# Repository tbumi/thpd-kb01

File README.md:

# thpd-kb01

My very first mechanical keyboard designed from scratch!

## PCB

The PCB design files are made with KiCad v5.1.12.

### Features

- STM32 Microcontroller (STM32F072C8T6)
- Rotary encoder
- USB-C connector
- NHD-C12832A1Z (128x32 LCD) display (not confirmed working)

## Case

The case files are made with Inkscape. They are available in the `case/` subdirectory.

## License

Licensed under the CERN Open Hardware Licence Version 2 - Strongly Reciprocal. A copy of
the license is included in this repository.

## Firmware

This keyboard uses the QMK firmware. See the firmware in the fork here:
https://github.com/tbumi/qmk_firmware/tree/thpd-kb01/keyboards/thpd_kb01

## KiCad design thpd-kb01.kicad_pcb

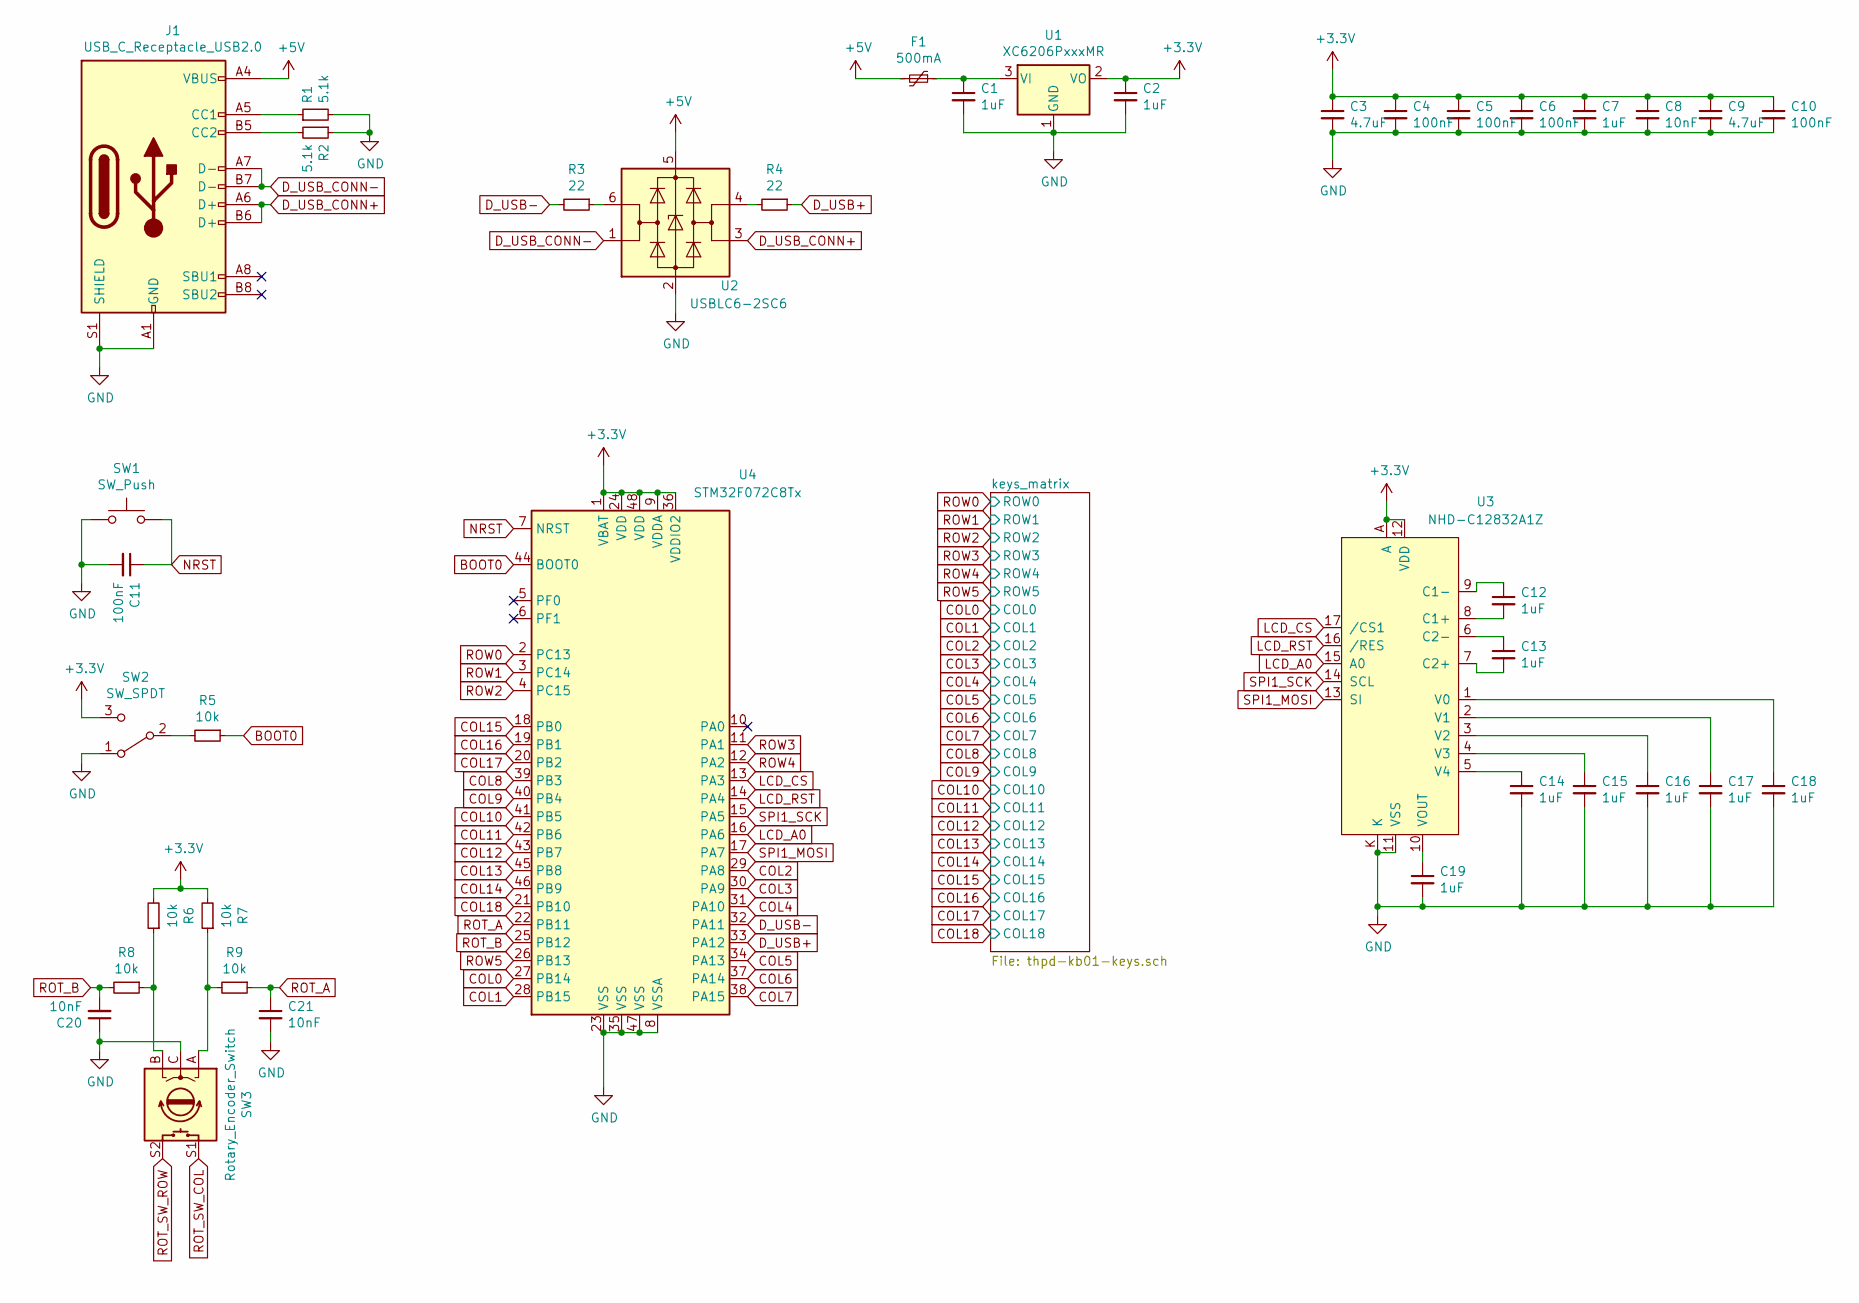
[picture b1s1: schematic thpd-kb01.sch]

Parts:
C1, C2, C7, C12, C13, C14, C15, C16, C17, C18, C19: 1uF; C_0402_1005Metric; LCSC Part # C52923
C3, C9: 4.7uF; C_0402_1005Metric; LCSC Part # C23733
C4, C5, C6, C10, C11: 100nF; C_0402_1005Metric; LCSC Part # C1525
C8, C20, C21: 10nF; C_0402_1005Metric; LCSC Part # C15195
F1: 500mA; Fuse_0603_1608Metric; LCSC Part # C135321
J1: USB_C_Receptacle_USB2.0; USB_C_Receptacle_HRO_TYPE-C-31-M-12; LCSC Part # C165948
R1, R2: 5.1k; R_0402_1005Metric; LCSC Part # C25905
R3, R4: 22; R_0402_1005Metric; LCSC Part # C25092
R5, R6, R7, R8, R9: 10k; R_0603_1608Metric; LCSC Part # C25804
SW1: SW_Push; SW_Push_SPST_NO_Alps_SKRK; LCSC Part # C202388
SW2: SW_SPDT; SW_SPDT_K3-1296S-E1; LCSC Part # C128955
SW3: Rotary_Encoder_Switch; RotaryEncoder_Alps_EC11E-Switch_Vertical_H20mm
U1: XC6206PxxxMR; SOT-23; LCSC Part # C5446
U2: USBLC6-2SC6; SOT-23-6; LCSC Part # C2827654
U3: NHD-C12832A1Z
U4: STM32F072C8Tx; LQFP-48_7x7mm_P0.5mm

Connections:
+3V3: C2.1, C3.1, C4.1, C5.1, C6.1, C7.1, C8.1, C9.1, C10.1, R6.2, R7.2, SW2.3 (C), U1.2 (VO), U3.12 (VDD), U3.A, U4.1 (VBAT), U4.9 (VDDA), U4.24 (VDD), U4.36 (VDDIO2), U4.48 (VDD)
+5V: F1.2, J1.A4 (VBUS), J1.A9 (VBUS), J1.B4 (VBUS), J1.B9 (VBUS), U2.5 (VBUS)
BOOT0: R5.1, U4.44 (BOOT0)
COL0: U4.27 (PB14); also elsewhere on the board
COL1: U4.28 (PB15); also elsewhere on the board
COL2: U4.29 (PA8); also elsewhere on the board
COL3: U4.30 (PA9); also elsewhere on the board
COL4: U4.31 (PA10); also elsewhere on the board
COL5: U4.34 (PA13); also elsewhere on the board
COL6: U4.37 (PA14); also elsewhere on the board
COL7: U4.38 (PA15); also elsewhere on the board
COL8: U4.39 (PB3); also elsewhere on the board
COL9: U4.40 (PB4); also elsewhere on the board
COL10: U4.41 (PB5); also elsewhere on the board
COL11: U4.42 (PB6); also elsewhere on the board
COL12: U4.43 (PB7); also elsewhere on the board
COL13: U4.45 (PB8); also elsewhere on the board
COL14: U4.46 (PB9); also elsewhere on the board
COL15: U4.18 (PB0); also elsewhere on the board
COL16: U4.19 (PB1); also elsewhere on the board
COL17: U4.20 (PB2); also elsewhere on the board
COL18: SW3.S1, U4.21 (PB10); also elsewhere on the board
D_USB+: R4.1, U4.33 (PA12)
D_USB-: R3.2, U4.32 (PA11)
D_USB_CONN+: J1.A6 (D+), J1.B6 (D+), U2.3 (I/O2)
D_USB_CONN-: J1.A7 (D-), J1.B7 (D-), U2.1 (I/O1)
GND: C1.2, C2.2, C3.2, C4.2, C5.2, C6.2, C7.2, C8.2, C9.2, C10.2, C11.2, C14.2, C15.2, C16.2, C17.2, C18.2, C19.2, C20.1, C21.2, J1.A1 (GND), J1.A12 (GND), J1.B1 (GND), J1.B12 (GND), J1.S1 (SHIELD), R1.2, R2.1, SW1.1, SW2.1 (A), SW3.C, U1.1 (GND), U2.2 (GND), U3.11 (VSS), U3.K, U4.8 (VSSA), U4.23 (VSS), U4.35 (VSS), U4.47 (VSS)
LCD_A0: U3.15 (A0), U4.16 (PA6)
LCD_CS: U3.17 (/CS1), U4.13 (PA3)
LCD_RST: U3.16 (/RES), U4.14 (PA4)
NRST: C11.1, SW1.2, U4.7 (NRST)
unnamed: C1.1, F1.1, U1.3 (VI)
unnamed: C12.1, U3.9 (C1-)
unnamed: C12.2, U3.8 (C1+)
unnamed: C13.1, U3.6 (C2-)
unnamed: C13.2, U3.7 (C2+)
unnamed: C14.1, U3.5 (V4)
unnamed: C15.1, U3.4 (V3)
unnamed: C16.1, U3.3 (V2)
unnamed: C17.1, U3.2 (V1)
unnamed: C18.1, U3.1 (V0)
unnamed: C19.1, U3.10 (VOUT)
unnamed: J1.A5 (CC1), R1.1
unnamed: J1.B5 (CC2), R2.2
unnamed: R3.1, U2.6 (I/O1)
unnamed: R4.2, U2.4 (I/O2)
unnamed: R5.2, SW2.2 (B)
unnamed: R6.1, R8.1, SW3.B
unnamed: R7.1, R9.2, SW3.A
ROT_A: C21.1, R9.1, U4.22 (PB11)
ROT_B: C20.2, R8.2, U4.25 (PB12)
ROT_SW_ROW: SW3.S2; also elsewhere on the board
ROW0: U4.2 (PC13); also elsewhere on the board
ROW1: U4.3 (PC14); also elsewhere on the board
ROW2: U4.4 (PC15); also elsewhere on the board
ROW3: U4.11 (PA1); also elsewhere on the board
ROW4: U4.12 (PA2); also elsewhere on the board
ROW5: U4.26 (PB13); also elsewhere on the board
SPI1_MOSI: U3.13 (SI), U4.17 (PA7)
SPI1_SCK: U3.14 (SCL), U4.15 (PA5)

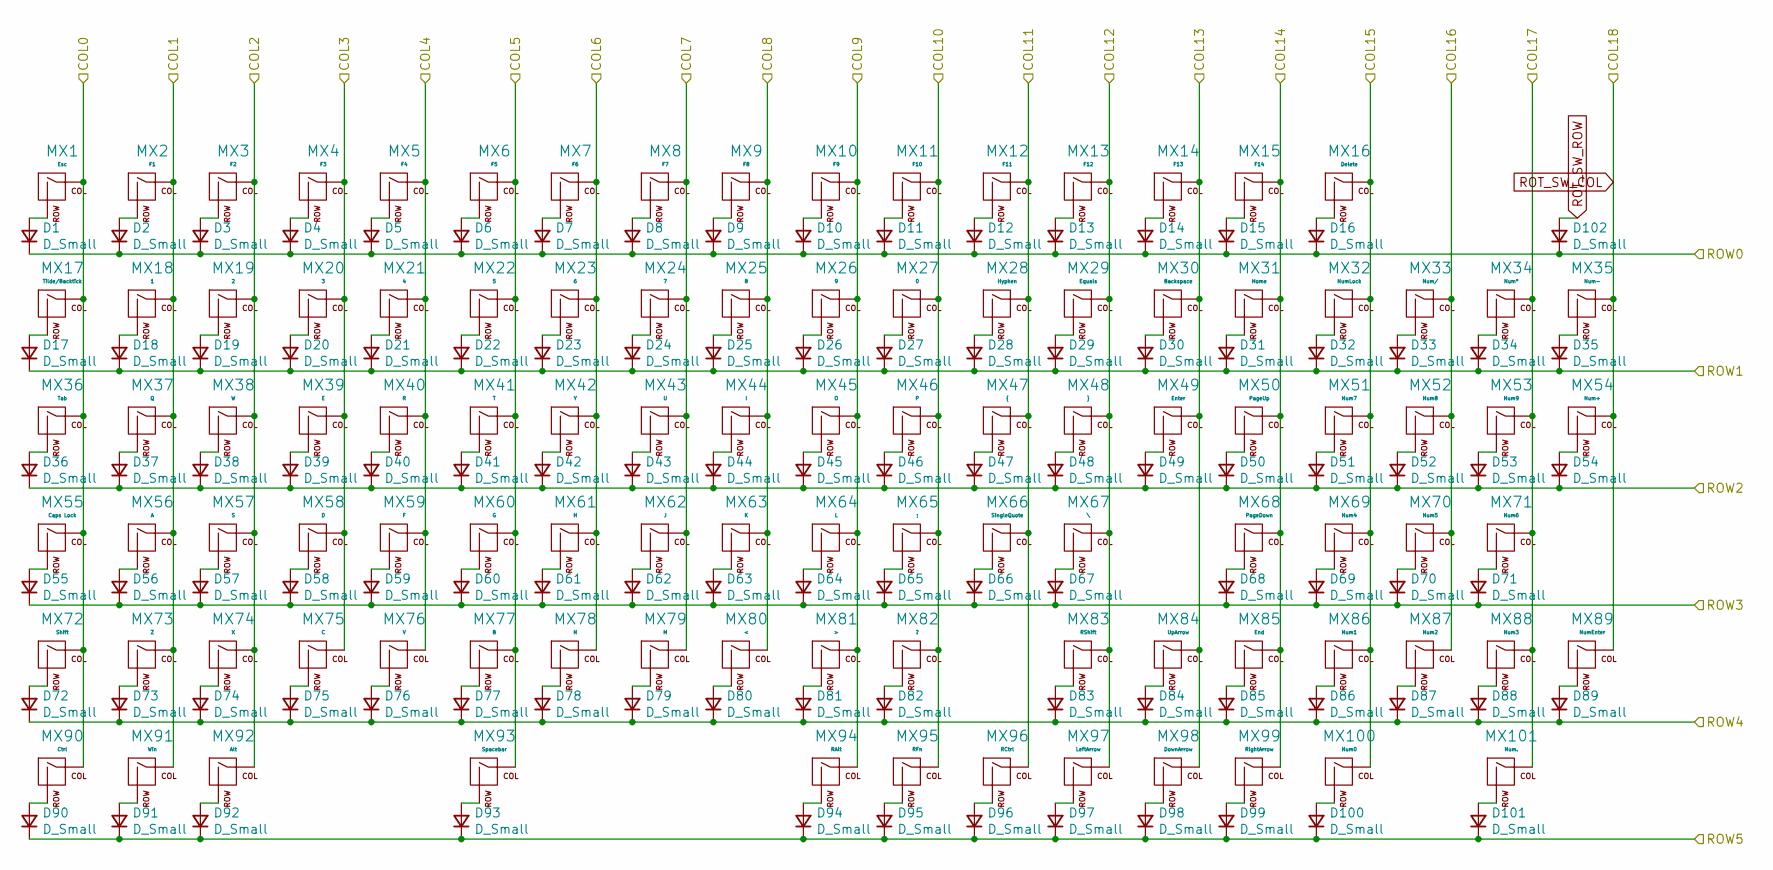
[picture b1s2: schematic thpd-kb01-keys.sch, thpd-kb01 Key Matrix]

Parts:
D1, D2, D3, D4, D5, D6, D7, D8, D9, D10, D11, D12, D13, D14, D15, D16, D17, D18, D19, D20, D21, D22, D23, D24, D25, D26, D27, D28, D29, D30, D31, D32, D33, D34, D35, D36, D37, D38, D39, D40, D41, D42, D43, D44, D45, D46, D47, D48, D49, D50, D51, D52, D53, D54, D55, D56, D57, D58, D59, D60, D61, D62, D63, D64, D65, D66, D67, D68, D69, D70, D71, D72, D73, D74, D75, D76, D77, D78, D79, D80, D81, D82, D83, D84, D85, D86, D87, D88, D89, D90, D91, D92, D93, D94, D95, D96, D97, D98, D99, D100, D101, D102: D_Small; D_SOD-123; LCSC Part # C81598
MX1: Esc; SW_Cherry_MX_1.00u_Plate
MX2: F1; SW_Cherry_MX_1.00u_Plate
MX3: F2; SW_Cherry_MX_1.00u_Plate
MX4: F3; SW_Cherry_MX_1.00u_Plate
MX5: F4; SW_Cherry_MX_1.00u_Plate
MX6: F5; SW_Cherry_MX_1.00u_Plate
MX7: F6; SW_Cherry_MX_1.00u_Plate
MX8: F7; SW_Cherry_MX_1.00u_Plate
MX9: F8; SW_Cherry_MX_1.00u_Plate
MX10: F9; SW_Cherry_MX_1.00u_Plate
MX11: F10; SW_Cherry_MX_1.00u_Plate
MX12: F11; SW_Cherry_MX_1.00u_Plate
MX13: F12; SW_Cherry_MX_1.00u_Plate
MX14: F13; SW_Cherry_MX_1.00u_Plate
MX15: F14; SW_Cherry_MX_1.00u_Plate
MX16: Delete; SW_Cherry_MX_1.00u_Plate
MX17: Tilde/Backtick; SW_Cherry_MX_1.00u_Plate
MX18: 1; SW_Cherry_MX_1.00u_Plate
MX19: 2; SW_Cherry_MX_1.00u_Plate
MX20: 3; SW_Cherry_MX_1.00u_Plate
MX21: 4; SW_Cherry_MX_1.00u_Plate
MX22: 5; SW_Cherry_MX_1.00u_Plate
MX23: 6; SW_Cherry_MX_1.00u_Plate
MX24: 7; SW_Cherry_MX_1.00u_Plate
MX25: 8; SW_Cherry_MX_1.00u_Plate
MX26: 9; SW_Cherry_MX_1.00u_Plate
MX27: 0; SW_Cherry_MX_1.00u_Plate
MX28: Hyphen; SW_Cherry_MX_1.00u_Plate
MX29: Equals; SW_Cherry_MX_1.00u_Plate
MX30: Backspace; SW_Cherry_MX_2.00u_Plate
MX31: Home; SW_Cherry_MX_1.00u_Plate
MX32: NumLock; SW_Cherry_MX_1.00u_Plate
MX33: Num/; SW_Cherry_MX_1.00u_Plate
MX34: Num*; SW_Cherry_MX_1.00u_Plate
MX35: Num-; SW_Cherry_MX_1.00u_Plate
MX36: Tab; SW_Cherry_MX_1.50u_Plate
MX37: Q; SW_Cherry_MX_1.00u_Plate
MX38: W; SW_Cherry_MX_1.00u_Plate
MX39: E; SW_Cherry_MX_1.00u_Plate
MX40: R; SW_Cherry_MX_1.00u_Plate
MX41: T; SW_Cherry_MX_1.00u_Plate
MX42: Y; SW_Cherry_MX_1.00u_Plate
MX43: U; SW_Cherry_MX_1.00u_Plate
MX44: I; SW_Cherry_MX_1.00u_Plate
MX45: O; SW_Cherry_MX_1.00u_Plate
MX46: P; SW_Cherry_MX_1.00u_Plate
MX47: {; SW_Cherry_MX_1.00u_Plate
MX48: }; SW_Cherry_MX_1.00u_Plate
MX49: Enter; SW_Cherry_MX_ISOEnter_Plate
MX50: PageUp; SW_Cherry_MX_1.00u_Plate
MX51: Num7; SW_Cherry_MX_1.00u_Plate
MX52: Num8; SW_Cherry_MX_1.00u_Plate
MX53: Num9; SW_Cherry_MX_1.00u_Plate
MX54: Num+; SW_Cherry_MX_2.00u_Vertical_Plate
MX55: Caps Lock; SW_Cherry_MX_1.75u_Plate
MX56: A; SW_Cherry_MX_1.00u_Plate
MX57: S; SW_Cherry_MX_1.00u_Plate
MX58: D; SW_Cherry_MX_1.00u_Plate
MX59: F; SW_Cherry_MX_1.00u_Plate
MX60: G; SW_Cherry_MX_1.00u_Plate
MX61: H; SW_Cherry_MX_1.00u_Plate
MX62: J; SW_Cherry_MX_1.00u_Plate
MX63: K; SW_Cherry_MX_1.00u_Plate
MX64: L; SW_Cherry_MX_1.00u_Plate
MX65: ;; SW_Cherry_MX_1.00u_Plate
MX66: SingleQuote; SW_Cherry_MX_1.00u_Plate
MX67: \\; SW_Cherry_MX_1.00u_Plate
MX68: PageDown; SW_Cherry_MX_1.00u_Plate
MX69: Num4; SW_Cherry_MX_1.00u_Plate
MX70: Num5; SW_Cherry_MX_1.00u_Plate
MX71: Num6; SW_Cherry_MX_1.00u_Plate
MX72: Shift; SW_Cherry_MX_2.25u_Plate
MX73: Z; SW_Cherry_MX_1.00u_Plate
MX74: X; SW_Cherry_MX_1.00u_Plate
MX75: C; SW_Cherry_MX_1.00u_Plate
MX76: V; SW_Cherry_MX_1.00u_Plate
MX77: B; SW_Cherry_MX_1.00u_Plate
MX78: N; SW_Cherry_MX_1.00u_Plate
MX79: M; SW_Cherry_MX_1.00u_Plate
MX80: <; SW_Cherry_MX_1.00u_Plate
MX81: >; SW_Cherry_MX_1.00u_Plate
MX82: ?; SW_Cherry_MX_1.00u_Plate
MX83: RShift; SW_Cherry_MX_1.75u_Plate
MX84: UpArrow; SW_Cherry_MX_1.00u_Plate
MX85: End; SW_Cherry_MX_1.00u_Plate
MX86: Num1; SW_Cherry_MX_1.00u_Plate
MX87: Num2; SW_Cherry_MX_1.00u_Plate
MX88: Num3; SW_Cherry_MX_1.00u_Plate
MX89: NumEnter; SW_Cherry_MX_2.00u_Vertical_Plate
MX90: Ctrl; SW_Cherry_MX_1.25u_Plate
MX91: Win; SW_Cherry_MX_1.25u_Plate
MX92: Alt; SW_Cherry_MX_1.25u_Plate
MX93: Spacebar; SW_Cherry_MX_6.25u_Plate
MX94: RAlt; SW_Cherry_MX_1.00u_Plate
MX95: RFn; SW_Cherry_MX_1.00u_Plate
MX96: RCtrl; SW_Cherry_MX_1.00u_Plate
MX97: LeftArrow; SW_Cherry_MX_1.00u_Plate
MX98: DownArrow; SW_Cherry_MX_1.00u_Plate
MX99: RightArrow; SW_Cherry_MX_1.00u_Plate
MX100: Num0; SW_Cherry_MX_2.00u_Plate
MX101: Num.; SW_Cherry_MX_1.00u_Plate

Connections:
COL0: MX1.1 (COL), MX17.1 (COL), MX36.1 (COL), MX55.1 (COL), MX72.1 (COL), MX90.1 (COL); also elsewhere on the board
COL1: MX2.1 (COL), MX18.1 (COL), MX37.1 (COL), MX56.1 (COL), MX73.1 (COL), MX91.1 (COL); also elsewhere on the board
COL2: MX3.1 (COL), MX19.1 (COL), MX38.1 (COL), MX57.1 (COL), MX74.1 (COL), MX92.1 (COL); also elsewhere on the board
COL3: MX4.1 (COL), MX20.1 (COL), MX39.1 (COL), MX58.1 (COL), MX75.1 (COL); also elsewhere on the board
COL4: MX5.1 (COL), MX21.1 (COL), MX40.1 (COL), MX59.1 (COL), MX76.1 (COL); also elsewhere on the board
COL5: MX6.1 (COL), MX22.1 (COL), MX41.1 (COL), MX60.1 (COL), MX77.1 (COL), MX93.1 (COL); also elsewhere on the board
COL6: MX7.1 (COL), MX23.1 (COL), MX42.1 (COL), MX61.1 (COL), MX78.1 (COL); also elsewhere on the board
COL7: MX8.1 (COL), MX24.1 (COL), MX43.1 (COL), MX62.1 (COL), MX79.1 (COL); also elsewhere on the board
COL8: MX9.1 (COL), MX25.1 (COL), MX44.1 (COL), MX63.1 (COL), MX80.1 (COL); also elsewhere on the board
COL9: MX10.1 (COL), MX26.1 (COL), MX45.1 (COL), MX64.1 (COL), MX81.1 (COL), MX94.1 (COL); also elsewhere on the board
COL10: MX11.1 (COL), MX27.1 (COL), MX46.1 (COL), MX65.1 (COL), MX82.1 (COL), MX95.1 (COL); also elsewhere on the board
COL11: MX12.1 (COL), MX28.1 (COL), MX47.1 (COL), MX66.1 (COL), MX96.1 (COL); also elsewhere on the board
COL12: MX13.1 (COL), MX29.1 (COL), MX48.1 (COL), MX67.1 (COL), MX83.1 (COL), MX97.1 (COL); also elsewhere on the board
COL13: MX14.1 (COL), MX30.1 (COL), MX49.1 (COL), MX84.1 (COL), MX98.1 (COL); also elsewhere on the board
COL14: MX15.1 (COL), MX31.1 (COL), MX50.1 (COL), MX68.1 (COL), MX85.1 (COL), MX99.1 (COL); also elsewhere on the board
COL15: MX16.1 (COL), MX32.1 (COL), MX51.1 (COL), MX69.1 (COL), MX86.1 (COL), MX100.1 (COL); also elsewhere on the board
COL16: MX33.1 (COL), MX52.1 (COL), MX70.1 (COL), MX87.1 (COL); also elsewhere on the board
COL17: MX34.1 (COL), MX53.1 (COL), MX71.1 (COL), MX88.1 (COL), MX101.1 (COL); also elsewhere on the board
COL18: MX35.1 (COL), MX54.1 (COL), MX89.1 (COL); also elsewhere on the board
unnamed: D1.2 (A), MX1.2 (ROW)
unnamed: D2.2 (A), MX2.2 (ROW)
unnamed: D3.2 (A), MX3.2 (ROW)
unnamed: D4.2 (A), MX4.2 (ROW)
unnamed: D5.2 (A), MX5.2 (ROW)
unnamed: D6.2 (A), MX6.2 (ROW)
unnamed: D7.2 (A), MX7.2 (ROW)
unnamed: D8.2 (A), MX8.2 (ROW)
unnamed: D9.2 (A), MX9.2 (ROW)
unnamed: D10.2 (A), MX10.2 (ROW)
unnamed: D11.2 (A), MX11.2 (ROW)
unnamed: D12.2 (A), MX12.2 (ROW)
unnamed: D13.2 (A), MX13.2 (ROW)
unnamed: D14.2 (A), MX14.2 (ROW)
unnamed: D15.2 (A), MX15.2 (ROW)
unnamed: D16.2 (A), MX16.2 (ROW)
unnamed: D17.2 (A), MX17.2 (ROW)
unnamed: D18.2 (A), MX18.2 (ROW)
unnamed: D19.2 (A), MX19.2 (ROW)
unnamed: D20.2 (A), MX20.2 (ROW)
unnamed: D21.2 (A), MX21.2 (ROW)
unnamed: D22.2 (A), MX22.2 (ROW)
unnamed: D23.2 (A), MX23.2 (ROW)
unnamed: D24.2 (A), MX24.2 (ROW)
unnamed: D25.2 (A), MX25.2 (ROW)
unnamed: D26.2 (A), MX26.2 (ROW)
unnamed: D27.2 (A), MX27.2 (ROW)
unnamed: D28.2 (A), MX28.2 (ROW)
unnamed: D29.2 (A), MX29.2 (ROW)
unnamed: D30.2 (A), MX30.2 (ROW)
unnamed: D31.2 (A), MX31.2 (ROW)
unnamed: D32.2 (A), MX32.2 (ROW)
unnamed: D33.2 (A), MX33.2 (ROW)
unnamed: D34.2 (A), MX34.2 (ROW)
unnamed: D35.2 (A), MX35.2 (ROW)
unnamed: D36.2 (A), MX36.2 (ROW)
unnamed: D37.2 (A), MX37.2 (ROW)
unnamed: D38.2 (A), MX38.2 (ROW)
unnamed: D39.2 (A), MX39.2 (ROW)
unnamed: D40.2 (A), MX40.2 (ROW)
unnamed: D41.2 (A), MX41.2 (ROW)
unnamed: D42.2 (A), MX42.2 (ROW)
unnamed: D43.2 (A), MX43.2 (ROW)
unnamed: D44.2 (A), MX44.2 (ROW)
unnamed: D45.2 (A), MX45.2 (ROW)
unnamed: D46.2 (A), MX46.2 (ROW)
unnamed: D47.2 (A), MX47.2 (ROW)
unnamed: D48.2 (A), MX48.2 (ROW)
unnamed: D49.2 (A), MX49.2 (ROW)
unnamed: D50.2 (A), MX50.2 (ROW)
unnamed: D51.2 (A), MX51.2 (ROW)
unnamed: D52.2 (A), MX52.2 (ROW)
unnamed: D53.2 (A), MX53.2 (ROW)
unnamed: D54.2 (A), MX54.2 (ROW)
unnamed: D55.2 (A), MX55.2 (ROW)
unnamed: D56.2 (A), MX56.2 (ROW)
unnamed: D57.2 (A), MX57.2 (ROW)
unnamed: D58.2 (A), MX58.2 (ROW)
unnamed: D59.2 (A), MX59.2 (ROW)
unnamed: D60.2 (A), MX60.2 (ROW)
unnamed: D61.2 (A), MX61.2 (ROW)
unnamed: D62.2 (A), MX62.2 (ROW)
unnamed: D63.2 (A), MX63.2 (ROW)
unnamed: D64.2 (A), MX64.2 (ROW)
unnamed: D65.2 (A), MX65.2 (ROW)
unnamed: D66.2 (A), MX66.2 (ROW)
unnamed: D67.2 (A), MX67.2 (ROW)
unnamed: D68.2 (A), MX68.2 (ROW)
unnamed: D69.2 (A), MX69.2 (ROW)
unnamed: D70.2 (A), MX70.2 (ROW)
unnamed: D71.2 (A), MX71.2 (ROW)
unnamed: D72.2 (A), MX72.2 (ROW)
unnamed: D73.2 (A), MX73.2 (ROW)
unnamed: D74.2 (A), MX74.2 (ROW)
unnamed: D75.2 (A), MX75.2 (ROW)
unnamed: D76.2 (A), MX76.2 (ROW)
unnamed: D77.2 (A), MX77.2 (ROW)
unnamed: D78.2 (A), MX78.2 (ROW)
unnamed: D79.2 (A), MX79.2 (ROW)
unnamed: D80.2 (A), MX80.2 (ROW)
unnamed: D81.2 (A), MX81.2 (ROW)
unnamed: D82.2 (A), MX82.2 (ROW)
unnamed: D83.2 (A), MX83.2 (ROW)
unnamed: D84.2 (A), MX84.2 (ROW)
unnamed: D85.2 (A), MX85.2 (ROW)
unnamed: D86.2 (A), MX86.2 (ROW)
unnamed: D87.2 (A), MX87.2 (ROW)
unnamed: D88.2 (A), MX88.2 (ROW)
unnamed: D89.2 (A), MX89.2 (ROW)
unnamed: D90.2 (A), MX90.2 (ROW)
unnamed: D91.2 (A), MX91.2 (ROW)
unnamed: D92.2 (A), MX92.2 (ROW)
unnamed: D93.2 (A), MX93.2 (ROW)
unnamed: D94.2 (A), MX94.2 (ROW)
unnamed: D95.2 (A), MX95.2 (ROW)
unnamed: D96.2 (A), MX96.2 (ROW)
unnamed: D97.2 (A), MX97.2 (ROW)
unnamed: D98.2 (A), MX98.2 (ROW)
unnamed: D99.2 (A), MX99.2 (ROW)
unnamed: D100.2 (A), MX100.2 (ROW)
unnamed: D101.2 (A), MX101.2 (ROW)
ROT_SW_ROW: D102.2 (A); also elsewhere on the board
ROW0: D1.1 (K), D2.1 (K), D3.1 (K), D4.1 (K), D5.1 (K), D6.1 (K), D7.1 (K), D8.1 (K), D9.1 (K), D10.1 (K), D11.1 (K), D12.1 (K), D13.1 (K), D14.1 (K), D15.1 (K), D16.1 (K), D102.1 (K); also elsewhere on the board
ROW1: D17.1 (K), D18.1 (K), D19.1 (K), D20.1 (K), D21.1 (K), D22.1 (K), D23.1 (K), D24.1 (K), D25.1 (K), D26.1 (K), D27.1 (K), D28.1 (K), D29.1 (K), D30.1 (K), D31.1 (K), D32.1 (K), D33.1 (K), D34.1 (K), D35.1 (K); also elsewhere on the board
ROW2: D36.1 (K), D37.1 (K), D38.1 (K), D39.1 (K), D40.1 (K), D41.1 (K), D42.1 (K), D43.1 (K), D44.1 (K), D45.1 (K), D46.1 (K), D47.1 (K), D48.1 (K), D49.1 (K), D50.1 (K), D51.1 (K), D52.1 (K), D53.1 (K), D54.1 (K); also elsewhere on the board
ROW3: D55.1 (K), D56.1 (K), D57.1 (K), D58.1 (K), D59.1 (K), D60.1 (K), D61.1 (K), D62.1 (K), D63.1 (K), D64.1 (K), D65.1 (K), D66.1 (K), D67.1 (K), D68.1 (K), D69.1 (K), D70.1 (K), D71.1 (K); also elsewhere on the board
ROW4: D72.1 (K), D73.1 (K), D74.1 (K), D75.1 (K), D76.1 (K), D77.1 (K), D78.1 (K), D79.1 (K), D80.1 (K), D81.1 (K), D82.1 (K), D83.1 (K), D84.1 (K), D85.1 (K), D86.1 (K), D87.1 (K), D88.1 (K), D89.1 (K); also elsewhere on the board
ROW5: D90.1 (K), D91.1 (K), D92.1 (K), D93.1 (K), D94.1 (K), D95.1 (K), D96.1 (K), D97.1 (K), D98.1 (K), D99.1 (K), D100.1 (K), D101.1 (K); also elsewhere on the board

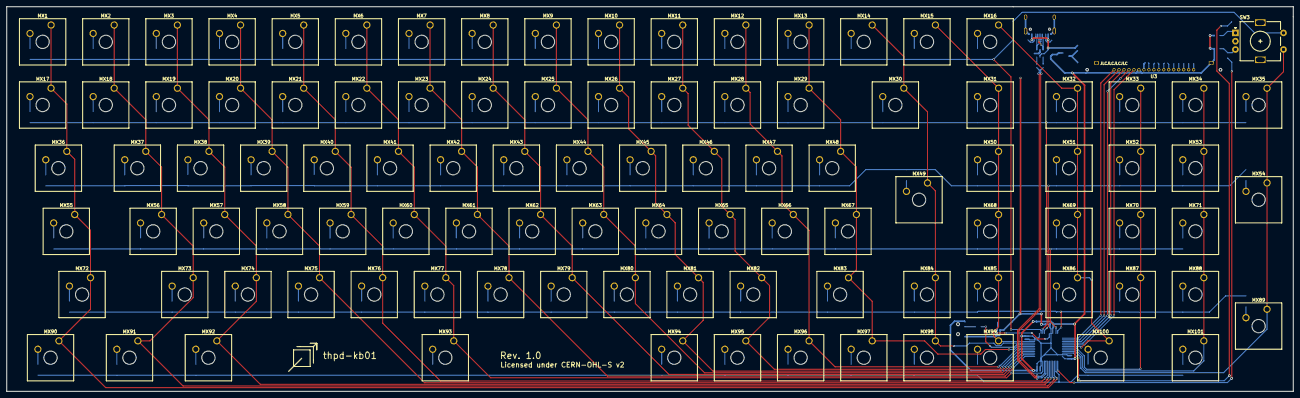
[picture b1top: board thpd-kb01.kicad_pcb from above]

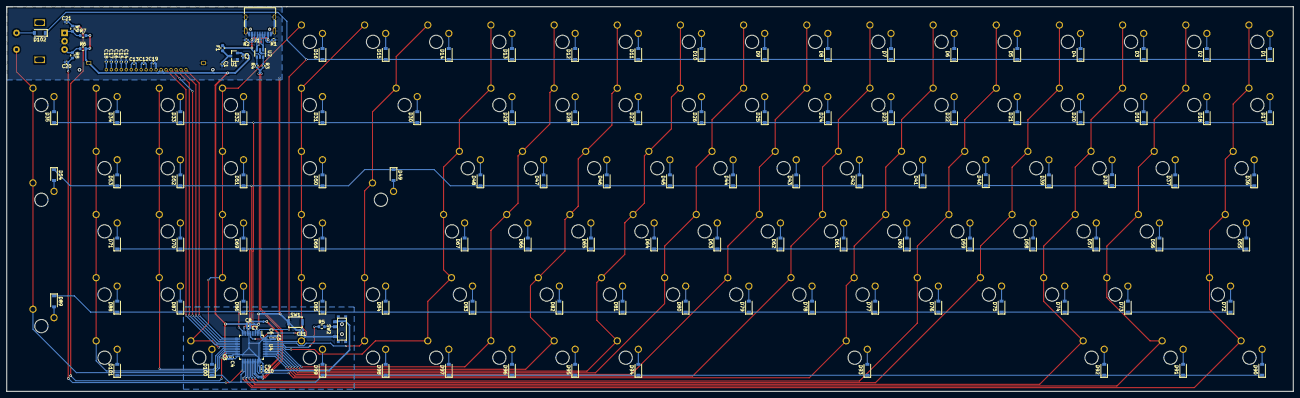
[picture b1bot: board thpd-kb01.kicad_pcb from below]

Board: 2 copper layers, 388.0 x 116.0 mm, 242 parts (139 on the bottom side), 161 nets.

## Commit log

2021-10-23 init project
2021-10-23 Add submodules
2021-10-23 add libraries
2021-10-23 WIP keys matrix
2021-10-25 wip pcb
2021-10-31 Switch USB B to USB C
2021-10-31 remove unnecessary submodules
2021-11-07 remove random-keyboard-parts from kicad
2021-11-07 remove random-keyboard-parts submodule
2021-11-07 re-add mx_alps library
2021-11-07 re-add mx_alps submodule lib
2021-11-18 Switch to STM32F072CBT6 MCU
2021-11-18 re-annotate symbols
2021-12-04 Big changes
2021-12-12 All routing except row/col done.
2021-12-15 Routing of rows and columns done.
2021-12-20 All routing complete.
2021-12-20 Add art.
2021-12-20 Add LCSC part numbers and prepared for output.
2022-01-04 Remove LEDs and redo routing from scratch.
2022-01-06 All DRC errors corrected.
2022-01-06 Final release to production.
2022-01-30 Case drafts (WIP)
2022-01-31 Case ready to print.
2022-02-12 Fix 5mm print file
2022-02-20 Add readme and LICENSE.
2022-02-20 Add license text to KiCad sources.
2022-02-20 Update readme.

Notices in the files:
thpd-kb01.kicad_pcb:
Copyright Trapsilo Bumi 2022
Licensed under the CERN-OHL-S v2
Licensed under CERN-OHL-S v2
